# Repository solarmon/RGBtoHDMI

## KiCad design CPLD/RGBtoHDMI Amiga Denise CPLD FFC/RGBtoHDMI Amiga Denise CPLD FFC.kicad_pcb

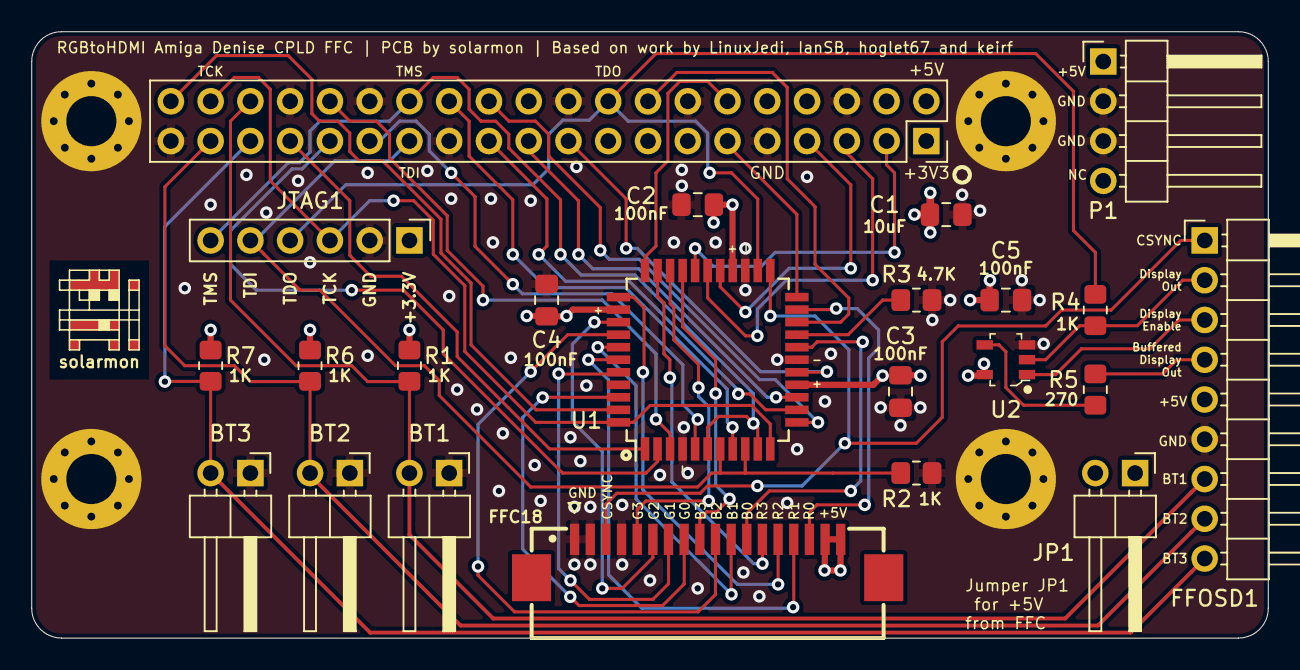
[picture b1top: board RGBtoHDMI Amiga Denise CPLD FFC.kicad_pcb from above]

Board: 2 copper layers, 79.0 x 38.7 mm, 28 parts (0 on the bottom side), 45 nets.

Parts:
BT1, BT2, BT3: Jumper_2_Open; PinHeader_1x02_P2.54mm_Horizontal
C1: 10uF; C_0805_2012Metric_Pad1.18x1.45mm_HandSolder
C2, C3, C4, C5: 100nF; C_0805_2012Metric_Pad1.18x1.45mm_HandSolder
FFC18: Conn_01x18; FPC-SMD_X10B25U18T
FFOSD1: Conn_01x09; PinHeader_1x09_P2.54mm_Horizontal
H1, H2, H3, H4: MountingHole_Pad; MountingHole_3.2mm_M3_Pad_Via
J1: Raspberry_Pi_2_3; PinSocket_2x20_P2.54mm_Vertical
JP1: Conn_01x02; PinHeader_1x02_P2.54mm_Horizontal
JTAG1: Conn_01x06; PinHeader_1x06_P2.54mm_Vertical
P1: Conn_01x04; PinHeader_1x04_P2.54mm_Horizontal
R1, R2, R4, R6, R7: 1K; R_0805_2012Metric_Pad1.20x1.40mm_HandSolder
R3: 4.7K; R_0805_2012Metric_Pad1.20x1.40mm_HandSolder
R5: 270; R_0805_2012Metric_Pad1.20x1.40mm_HandSolder
U1: XC9572VQ44 or XC9572XL-10VQG44C; TQFP-44_10x10mm_P0.8mm
U2: 74LVC1G125; SOT-753
solarmon: solarmon-logo-25mils

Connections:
+3V3: C1.1, C2.1, C3.1, C4.1, C5.1, J1.1, J1.17, JTAG1.1, R1.1, R6.1, R7.1, U1.15, U1.26, U1.35, U2.5
+5V: FFOSD1.5, J1.2, J1.4, JP1.1, P1.1
/B0: FFC18.12, U1.18
/B1: FFC18.11, U1.38
/B2: FFC18.10, U1.37
/B3: FFC18.9, U1.30
/CLKEN: J1.28, JTAG1.6, U1.6, U1.10
/CSYNC: FFC18.3, FFOSD1.1, U1.23
/DETECT: R3.1, U1.19
/FFC_5V: FFC18.17, FFC18.18, JP1.2
/G0: FFC18.8, U1.42
/G1: FFC18.7, U1.40
/G2: FFC18.6, U1.36
/G3: FFC18.5, U1.31
/GPIO0: J1.27, JTAG1.5, R2.1, U1.7, U1.9
/GPIO2: J1.3, U1.29
/GPIO3: J1.5, U1.28
/GPIO4: J1.7, U1.27
/GPIO5: J1.29, U1.5
/GPIO6: J1.31, U1.2
/GPIO7: J1.26, U1.8
/GPIO8: J1.24, U1.12
/GPIO9: J1.21, U1.14
/GPIO10: J1.19, U1.16
/GPIO11: J1.23, U1.13
/GPIO12: J1.32, U1.3
/GPIO13: J1.33, U1.1
/GPIO16: BT1.2, FFOSD1.7, J1.36, R1.2
/GPIO17: J1.11, U1.22
/GPIO18: J1.12, U1.33
/GPIO19: BT3.2, FFOSD1.9, J1.35, R7.2
/GPIO20: J1.38, JTAG1.3, U1.11, U1.44
/GPIO21: J1.40, U1.43
/GPIO23: J1.16, U1.20
/GPIO24: J1.18, JTAG1.4, R4.1, U1.24
/GPIO26: BT2.2, FFOSD1.8, J1.37, R6.2
/OSD_DISPLAY_ENABLE: FFOSD1.3, U2.1
/OSD_DISPLAY_OUPUT: FFOSD1.2, R4.2, U2.2
/OSD_DISPLAY_OUTPUT_BUFFERRED: FFOSD1.4, R5.1
/R0: FFC18.16, U1.21
/R1: FFC18.15, U1.39
/R2: FFC18.14, U1.34
/R3: FFC18.13, U1.32
GND: BT1.1, BT2.1, BT3.1, C1.2, C2.2, C3.2, C4.2, C5.2, FFC18.1, FFC18.2, FFC18.4, FFOSD1.6, H1.1, H2.1, H3.1, H4.1, J1.6, J1.9, J1.14, J1.20, J1.25, J1.30, J1.34, J1.39, JTAG1.2, P1.2, P1.3, R2.2, R3.2, U1.4, U1.17, U1.25, U2.3
unnamed: R5.2, U2.4

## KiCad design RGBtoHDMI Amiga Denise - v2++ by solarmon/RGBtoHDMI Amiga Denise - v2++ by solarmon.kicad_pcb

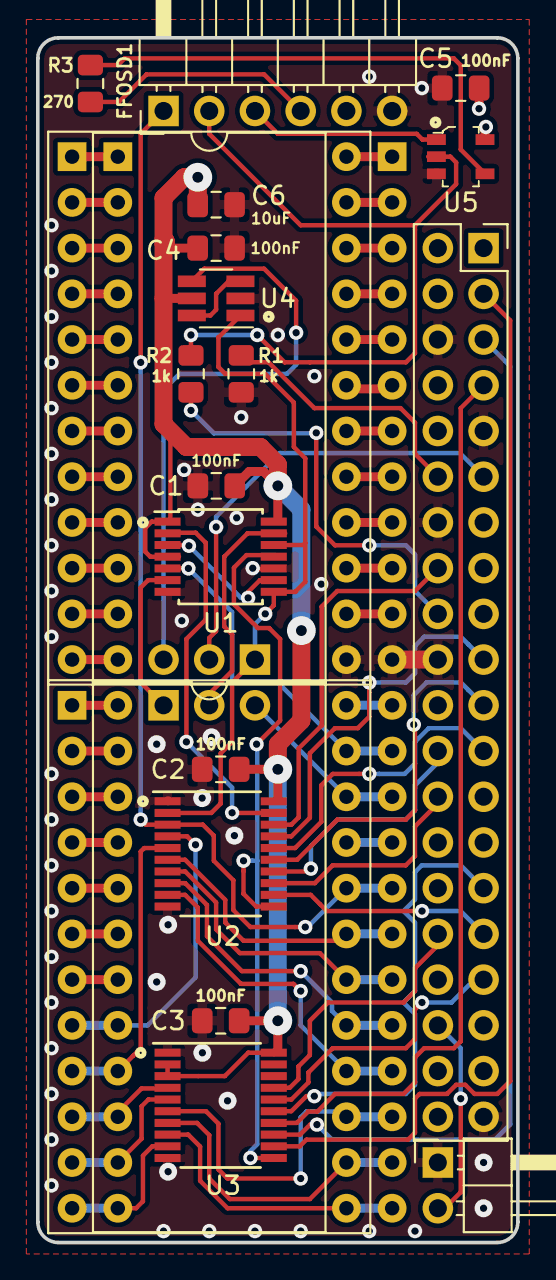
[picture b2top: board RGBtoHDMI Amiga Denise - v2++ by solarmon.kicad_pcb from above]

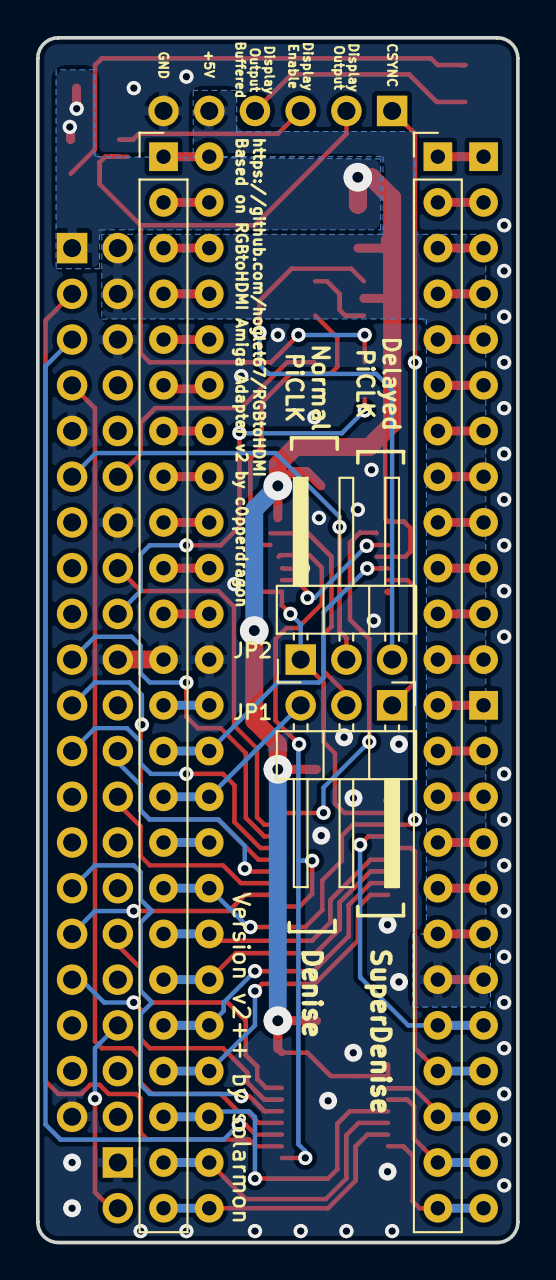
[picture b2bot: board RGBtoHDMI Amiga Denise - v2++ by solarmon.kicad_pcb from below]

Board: 2 copper layers, 26.7 x 66.9 mm, 23 parts (4 on the bottom side), 78 nets.

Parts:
C1, C2, C3, C4, C5: 100nF; C_0805_2012Metric_Pad1.15x1.40mm_HandSolder
C6: 10uF; C_0805_2012Metric_Pad1.15x1.40mm_HandSolder
FFOSD1: Conn_01x06; PinHeader_1x06_P2.54mm_Horizontal
JB1: Conn_01x02; PinHeader_1x02_P2.54mm_Horizontal
JDenise1, JDenise2: Conn_02x12_Counter_Clockwise; DIP-24_W15.24mm_Socket
JMainBoard1, JMainBoard2: Conn_01x24; PinHeader_1x24_P2.54mm_Vertical_smaller
JP1, JP2: Jumper_3_Bridged12; PinHeader_1x03_P2.54mm_Horizontal
JRaspberryPiZero1: Conn_02x20_Odd_Even; PinSocket_2x20_P2.54mm_Vertical
R1, R2: 1k; R_0805_2012Metric_Pad1.15x1.40mm_HandSolder
R3: 270; R_0805_2012Metric_Pad1.15x1.40mm_HandSolder
U1: 74LVC86; TSSOP-14_4.4x5mm_P0.65mm
U2, U3: 74LVC574; TSSOP-20_4.4x6.5mm_P0.65mm
U4: SN74LVC2G04; SOT-23-6_Handsoldering
U5: 74LVC1G125; SOT-753

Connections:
+3V3: C1.1, C2.1, C3.1, C4.1, C5.1, C6.1, JRaspberryPiZero1.1, U1.1, U1.4, U1.14, U2.20, U3.2, U3.3, U3.20, U4.5, U5.5
+5V: FFOSD1.5, JDenise2.7, JMainBoard1.19, JRaspberryPiZero1.2, JRaspberryPiZero1.4
/7MHZ: JDenise2.23, JMainBoard2.14, U1.5
/B0: JDenise2.12, JMainBoard1.24, U3.9
/B1: JDenise2.13, JMainBoard2.24, U3.8
/B2: JDenise2.14, JMainBoard2.23, U3.7
/B3: JDenise2.15, JMainBoard2.22, U3.6
/CDAC: JDenise2.22, JMainBoard2.15, JP1.3
/CSYNC: FFOSD1.1, JDenise2.20, JMainBoard2.17, U2.3
/G0: JDenise2.16, JMainBoard2.21, U2.9
/G1: JDenise2.17, JMainBoard2.20, U2.8
/G2: JDenise2.18, JMainBoard2.19, U2.7
/G3: JDenise2.19, JMainBoard2.18, U2.6
/OSD_DISPLAY_ENABLE: FFOSD1.3, U5.1
/OSD_DISPLAY_OUPUT: FFOSD1.2, R2.2, U5.2
/OSD_DISPLAY_OUTPUT_BUFFERRED: FFOSD1.4, R3.1
/PiB0: JRaspberryPiZero1.3, U3.12
/PiB1: JRaspberryPiZero1.5, U3.13
/PiB2: JRaspberryPiZero1.7, U3.14
/PiB3: JRaspberryPiZero1.29, U3.15
/PiCLK: JP2.2, JRaspberryPiZero1.11
/PiCSYNC: JRaspberryPiZero1.16, U2.18
/PiG0: JRaspberryPiZero1.31, U2.12
/PiG1: JRaspberryPiZero1.26, U2.13
/PiG2: JRaspberryPiZero1.24, U2.14
/PiG3: JRaspberryPiZero1.21, U2.15
/PiR0: JRaspberryPiZero1.19, U2.17
/PiR1: JRaspberryPiZero1.23, U2.16
/PiR2: JRaspberryPiZero1.32, U3.17
/PiR3: JRaspberryPiZero1.33, U3.16
/R0: JDenise2.8, JMainBoard1.20, U2.4
/R1: JDenise2.9, JMainBoard1.21, U2.5
/R2: JDenise2.10, JMainBoard1.22, U3.4
/R3: JDenise2.11, JMainBoard1.23, U3.5
GND: C1.2, C2.2, C3.2, C4.2, C5.2, C6.2, FFOSD1.6, JB1.1, JDenise1.13, JMainBoard2.12, JRaspberryPiZero1.6, JRaspberryPiZero1.9, JRaspberryPiZero1.14, JRaspberryPiZero1.20, JRaspberryPiZero1.39, R1.2, U1.7, U1.10, U2.1, U2.10, U3.1, U3.10, U4.2, U5.3
unnamed: JB1.2, JRaspberryPiZero1.36
unnamed: JDenise1.1, JMainBoard1.1
unnamed: JDenise1.2, JMainBoard1.2
unnamed: JDenise1.3, JMainBoard1.3
unnamed: JDenise1.4, JMainBoard1.4
unnamed: JDenise1.5, JMainBoard1.5
unnamed: JDenise1.6, JMainBoard1.6
unnamed: JDenise1.7, JMainBoard1.7
unnamed: JDenise1.8, JMainBoard1.8
unnamed: JDenise1.9, JMainBoard1.9
unnamed: JDenise1.10, JMainBoard1.10
unnamed: JDenise1.11, JMainBoard1.11
unnamed: JDenise1.12, JMainBoard1.12
unnamed: JDenise1.14, JMainBoard2.11
unnamed: JDenise1.15, JMainBoard2.10
unnamed: JDenise1.16, JMainBoard2.9
unnamed: JDenise1.17, JMainBoard2.8
unnamed: JDenise1.18, JMainBoard2.7
unnamed: JDenise1.19, JMainBoard2.6
unnamed: JDenise1.20, JMainBoard2.5
unnamed: JDenise1.21, JMainBoard2.4
unnamed: JDenise1.22, JMainBoard2.3
unnamed: JDenise1.23, JMainBoard2.2
unnamed: JDenise1.24, JMainBoard2.1
unnamed: JDenise2.1, JMainBoard1.13
unnamed: JDenise2.2, JMainBoard1.14
unnamed: JDenise2.3, JMainBoard1.15
unnamed: JDenise2.4, JMainBoard1.16
unnamed: JDenise2.5, JMainBoard1.17
unnamed: JDenise2.6, JMainBoard1.18
unnamed: JDenise2.21, JMainBoard2.16
unnamed: JDenise2.24, JMainBoard2.13
unnamed: JP1.1, U1.6
unnamed: JP1.2, U1.13
unnamed: JP2.1, U1.8, U1.12, U2.2, U4.1
unnamed: JP2.3, U4.4
unnamed: JRaspberryPiZero1.12, R1.1
unnamed: JRaspberryPiZero1.18, R2.1
unnamed: R3.2, U5.4
unnamed: U1.2, U2.19
unnamed: U1.3, U1.9
unnamed: U1.11, U2.11, U3.11
unnamed: U4.3, U4.6

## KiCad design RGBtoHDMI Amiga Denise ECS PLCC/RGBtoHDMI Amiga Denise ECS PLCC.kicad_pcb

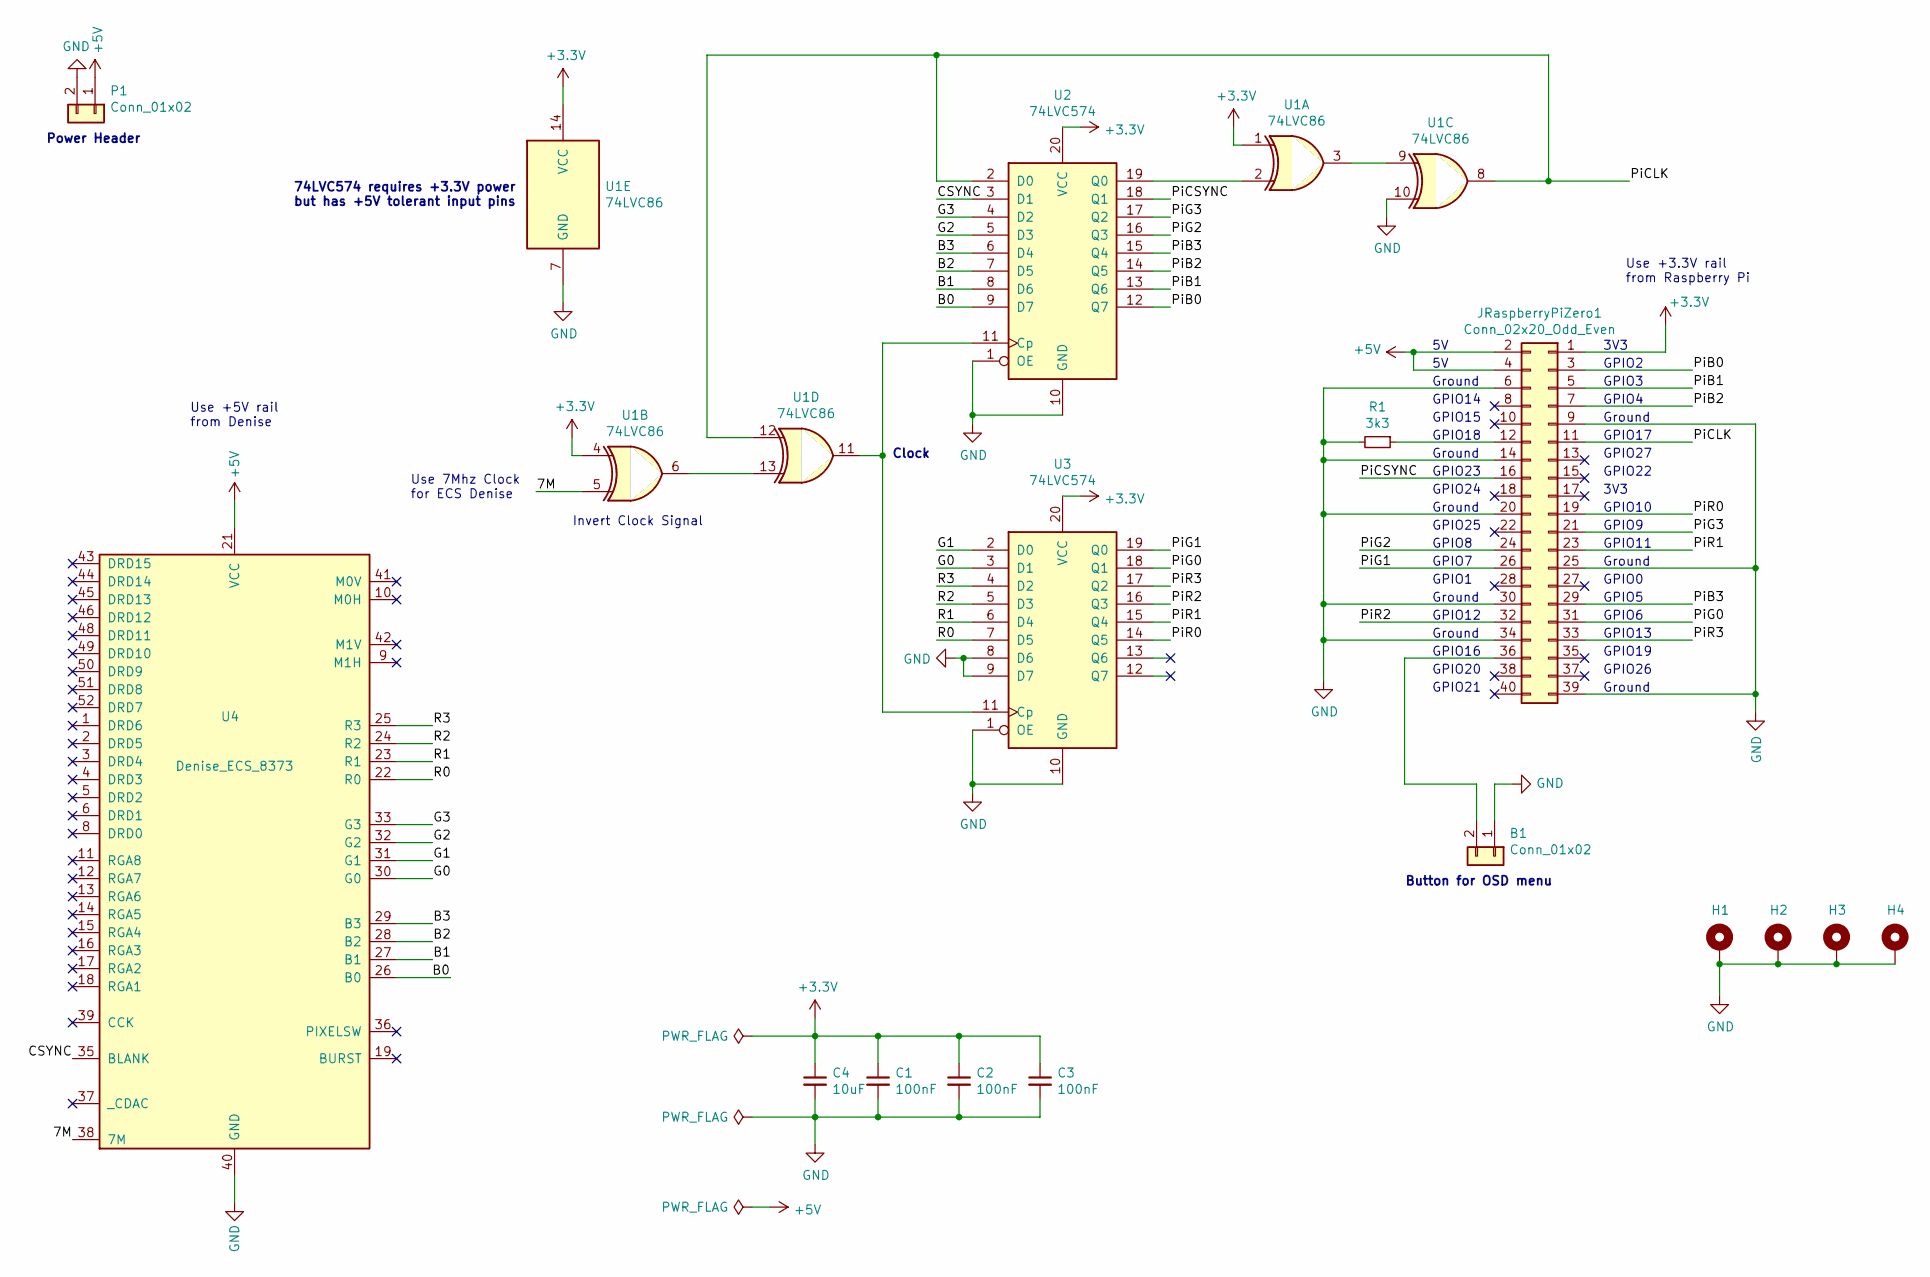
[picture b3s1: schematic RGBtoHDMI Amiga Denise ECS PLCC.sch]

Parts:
B1: Conn_01x02; PinHeader_1x02_P2.54mm_Vertical
C1, C2, C3: 100nF; C_0805_2012Metric_Pad1.15x1.40mm_HandSolder
C4: 10uF; C_0805_2012Metric_Pad1.15x1.40mm_HandSolder
H1, H2, H3, H4: MountingHole_Pad; MountingHole_3.2mm_M3_Pad
JRaspberryPiZero1: Conn_02x20_Odd_Even; PinSocket_2x20_P2.54mm_Vertical
P1: Conn_01x02; PinHeader_1x02_P2.54mm_Vertical
R1: 3k3; R_0805_2012Metric_Pad1.15x1.40mm_HandSolder
U1: 74LVC86; SOIC-14_3.9x8.7mm_P1.27mm
U2, U3: 74LVC574; SO-20_12.8x7.5mm_P1.27mm
U4: Denise_ECS_8373; PLCC-52_THT-Socket_Reversed_Hat

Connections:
+3V3: C1.1, C2.1, C3.1, C4.1, JRaspberryPiZero1.1, U1.1, U1.4, U1.14 (VCC), U2.20 (VCC), U3.20 (VCC)
+5V: JRaspberryPiZero1.2, JRaspberryPiZero1.4, P1.1, U4.21 (VCC)
/7M: U1.5, U4.38 (7M)
/B0: U2.9 (D7), U4.26 (B0)
/B1: U2.8 (D6), U4.27 (B1)
/B2: U2.7 (D5), U4.28 (B2)
/B3: U2.6 (D4), U4.29 (B3)
/CSYNC: U2.3 (D1), U4.35 (BLANK)
/G0: U3.3 (D1), U4.30 (G0)
/G1: U3.2 (D0), U4.31 (G1)
/G2: U2.5 (D3), U4.32 (G2)
/G3: U2.4 (D2), U4.33 (G3)
/PiB0: JRaspberryPiZero1.3, U2.12 (Q7)
/PiB1: JRaspberryPiZero1.5, U2.13 (Q6)
/PiB2: JRaspberryPiZero1.7, U2.14 (Q5)
/PiB3: JRaspberryPiZero1.29, U2.15 (Q4)
/PiCLK: JRaspberryPiZero1.11, U1.8, U1.12, U2.2 (D0)
/PiCSYNC: JRaspberryPiZero1.16, U2.18 (Q1)
/PiG0: JRaspberryPiZero1.31, U3.18 (Q1)
/PiG1: JRaspberryPiZero1.26, U3.19 (Q0)
/PiG2: JRaspberryPiZero1.24, U2.16 (Q3)
/PiG3: JRaspberryPiZero1.21, U2.17 (Q2)
/PiR0: JRaspberryPiZero1.19, U3.14 (Q5)
/PiR1: JRaspberryPiZero1.23, U3.15 (Q4)
/PiR2: JRaspberryPiZero1.32, U3.16 (Q3)
/PiR3: JRaspberryPiZero1.33, U3.17 (Q2)
/R0: U3.7 (D5), U4.22 (R0)
/R1: U3.6 (D4), U4.23 (R1)
/R2: U3.5 (D3), U4.24 (R2)
/R3: U3.4 (D2), U4.25 (R3)
GND: B1.1, C1.2, C2.2, C3.2, C4.2, H1.1, H2.1, H3.1, H4.1, JRaspberryPiZero1.6, JRaspberryPiZero1.9, JRaspberryPiZero1.14, JRaspberryPiZero1.20, JRaspberryPiZero1.25, JRaspberryPiZero1.30, JRaspberryPiZero1.34, JRaspberryPiZero1.39, P1.2, R1.2, U1.7 (GND), U1.10, U2.1 (OE), U2.10 (GND), U3.1 (OE), U3.8 (D6), U3.9 (D7), U3.10 (GND), U4.40 (GND)
unnamed: B1.2, JRaspberryPiZero1.36
unnamed: JRaspberryPiZero1.12, R1.1
unnamed: U1.2, U2.19 (Q0)
unnamed: U1.3, U1.9
unnamed: U1.11, U2.11 (Cp), U3.11 (Cp)
unnamed: U1.6, U1.13

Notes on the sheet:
3V3
Ground
GPIO14
GPIO15
GPIO18
GPIO23
GPIO24
GPIO25
GPIO8
GPIO7
GPIO1
GPIO12
GPIO16
GPIO21
GPIO20
GPIO2
GPIO3
GPIO4
GPIO17
GPIO27
GPIO22
GPIO10
GPIO9
GPIO11
GPIO0
GPIO5
GPIO6
GPIO13
GPIO19
GPIO26
74LVC574 requires +3.3V power but has +5V tolerant input pins
Clock
Invert Clock Signal
Use 7Mhz Clock for ECS Denise
Use +3.3V rail from Raspberry Pi
Use +5V rail from Denise
Button for OSD menu
Power Header

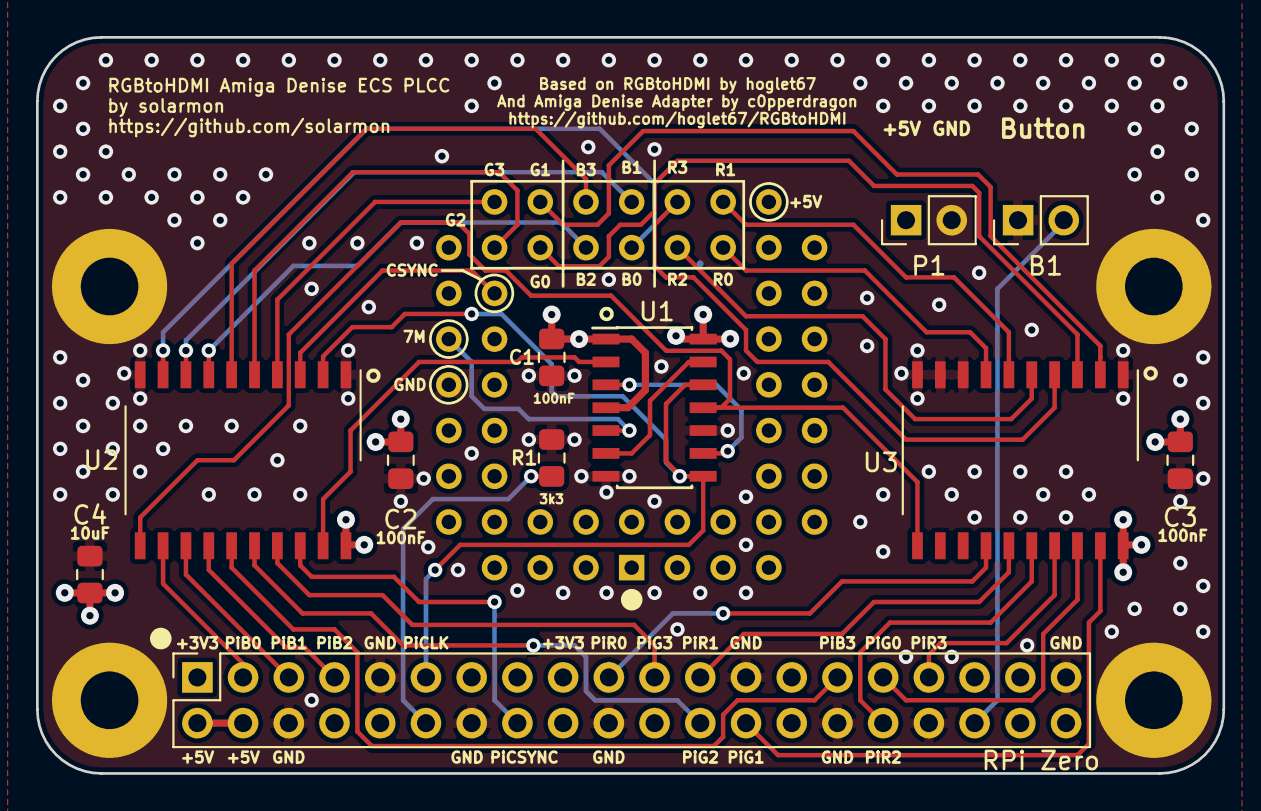
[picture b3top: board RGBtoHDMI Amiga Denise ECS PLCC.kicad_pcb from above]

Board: 2 copper layers, 65.9 x 40.9 mm, 16 parts (1 on the bottom side), 37 nets.
